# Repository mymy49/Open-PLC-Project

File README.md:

# Open-PLC-Project
yss OS를 사용한 오픈 소스/회로 PLC 프로젝트입니다.

중국의 [LCSC ELECTRONICS](https://www.lcsc.com/)에서 '전자 부품' + 'PCB' + 'SMT' 주문을 한번에 진행할 수 있는 자료를 모두 오픈할 계획입니다. 
누구나 PCB를 주문해서 거의 완성된 상태로 받아볼 수 있도록 할 계획입니다.
보드의 전체 기능이 yss OS 기반에서 제어 가능한 소스코드를 다운로드하여 필요한 동작을 구현하는 프로젝트입니다.

# 사용 프로그램
* 회로도/PCB : Kicad (<https://www.kicad.org/>)
* Compiler + IDE : gcc + Crossworks for ARM (<https://www.rowley.co.uk/arm/index.htm>)
* Office : Libreoffice (<https://www.libreoffice.org/>)

# Base Board
Base Board는 기본적인 소량의 디지털 I/O, 릴레이, AIN, AOUT을 갖출 계획입니다. 
부족한 기능은 외부에 보드를 추가해 CAN으로 서로 통신하며 기능을 보완하는 것을 계획하고 있습니다.

케이스 : <https://ko.aliexpress.com/item/1005003779239575.html?spm=a2g0o.order_list.order_list_main.5.185e140fnb0dcr&gatewayAdapt=glo2kor>

## 단자 구성
케이스는 총 40핀으로 구성되어 있습니다. 
핀맵은 아래와 같이 구성됩니다.

1. [전원] +8~24V (프리볼트)
2. [전원] GND
3. [통신] CANL
4. [통신] CANH

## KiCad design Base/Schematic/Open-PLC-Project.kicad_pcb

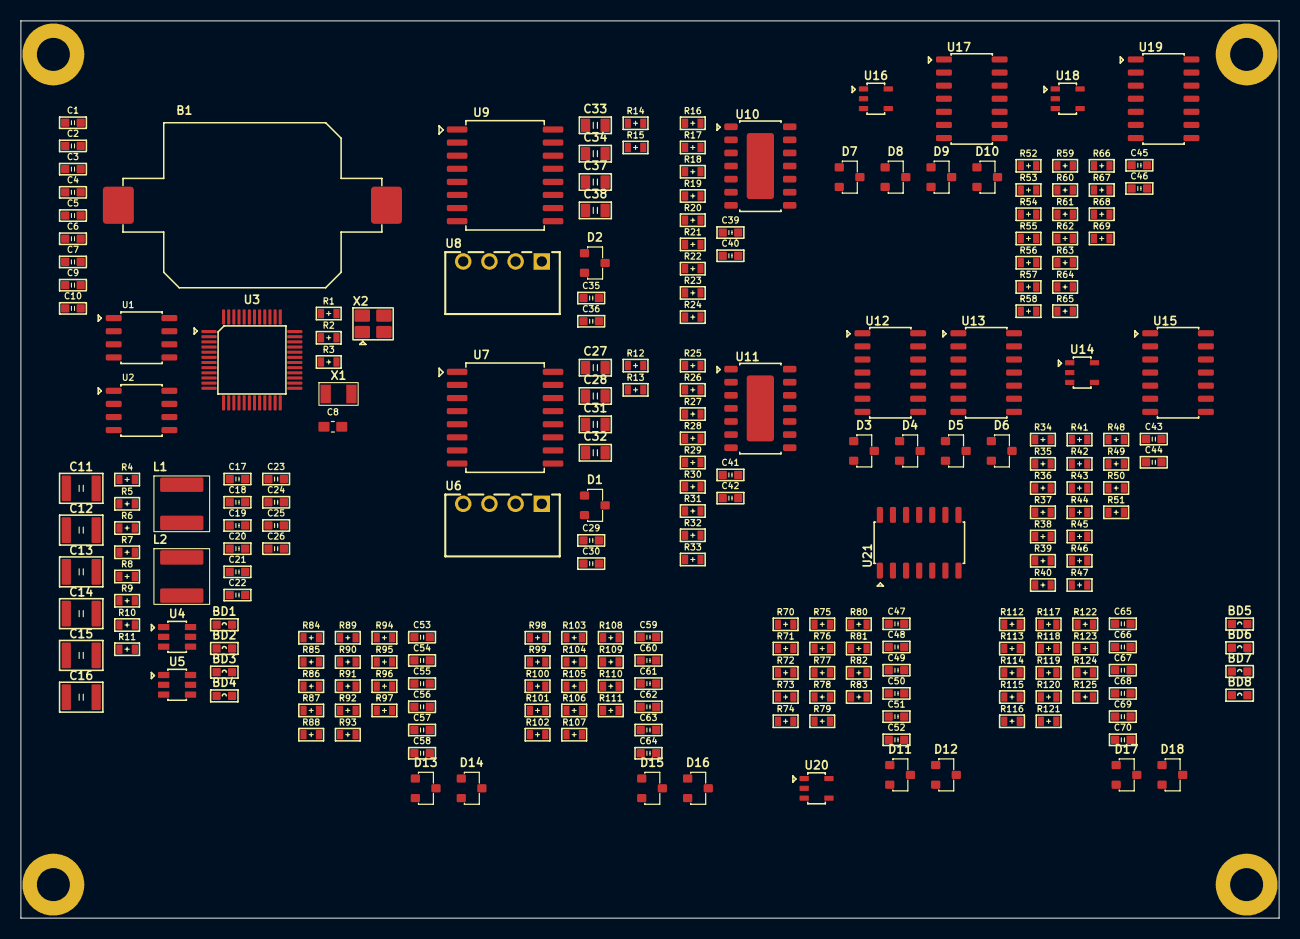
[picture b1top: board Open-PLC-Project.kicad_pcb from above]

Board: 2 copper layers, 122.0 x 87.0 mm, 251 parts (0 on the bottom side), 140 nets, no tracks yet.

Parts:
B1: GT-CR1632-1Au
BD1, BD2, BD3, BD4, BD5, BD6, BD7, BD8: BLM18KG121TN1D; 0603
C1, C4, C7, C9, C10, C17, C18, C19, C20, C21, C22, C29, C30, C35, C36, C40, C42, C43, C44, C45, C46, C47, C51, C52, C53, C57, C58, C59, C63, C64, C65, C69, C70: 0603B104K500; 0603
C2, C3, C5, C6: 0603N120J500; 0603
C8: 0603X225K100; C_0603_1608Metric_Pad1.08x0.95mm_HandSolder
C11, C12, C13, C14, C15, C16: 1210B225K101; 1210
C23, C24, C25, C26: 0603X106K100; 0603
C27, C28, C33, C34: 1206B225K500; 0805
C31, C32, C37, C38: 0805B475K160; 0805
C39, C41, C48, C49, C50, C54, C55, C56, C60, C61, C62, C66, C67, C68: 0603B101K500; 0603
D1: NUP2105LT1G; SOT23
D2: PSM712-ES; SOT23
D3, D4, D5, D6, D7, D8, D9, D10, D11, D12, D13, D14, D15, D16, D17, D18: KDS226; SOT23
H1, H2, H3, H4: HOLE-PAD-7.0-3.2; Hole_7_0_3_2
L1, L2: SWPA5040S150MT; SWPA5040S
R1, R2, R23, R32, R34, R36, R37, R38, R39, R40, R41, R42, R43, R44, R45, R46, R47, R52, R54, R55, R56, R57, R58, R59, R60, R61, R62, R63, R64, R65: WR06X4701FTL; 0603
R3: WR06W3R30FTL; 0603
R4, R6: WR06X4123FTL; 0603
R5, R7: WR06X2003FTL; 0603
R8: WR06X8872FTL; 0603
R9, R11: WR06X2212FTL; 0603
R10: WR06X5102FTL; 0603
R12, R13, R14, R15: WR06X0000JTL; 0603
R16, R17, R18, R19, R20, R21, R22, R25, R26, R27, R28, R29, R30, R31, R48, R49, R50, R51, R66, R67, R68, R69, R70, R71, R72, R73, R78, R79, R80, R81, R84, R85, R86, R87, R92, R93, R94, R95, R98, R99, R100, R101, R106, R107, R108, R109, R112, R113, R114, R115, R120, R121, R122, R123: WR06X1002FTL; 0603
R24, R33: WR06X1201FTL; 0603
R35, R53: WR06X4700FTL; 0603
R74, R75, R76, R77, R88, R89, R90, R91, R102, R103, R104, R105, R116, R117, R118, R119: WR06X3302FTL; 0603
R82, R83, R96, R97, R110, R111, R124, R125: WR06X1001FTL; 0603
U1: MB85RC16PNF-G-JNE; SOIC-8
U2: SL1307ZN+T; SOIC-8
U3: M433LE8AE; LQFP48
U4, U5: TPS560430XDBV; DBV0006A
U6, U8: B0505S-1W; BXXS-1W
U7: CA-IS3052CW; SOIC-16-WB
U9: CA-IS3082WX; SOIC-16-WB
U10, U11: BTS5200-4EKA; PG-DSO-14-48-EP
U12, U13: LM239DR2G; SOIC-14
U14, U16, U18, U20: LMV321-TR; SOT-23-5L
U15, U17, U19, U21: TP2584-SR; SOIC-14
X1: XKXGI-SUA-32.768K; SMD_3215_2Pin
X2: 1532H4-12000JWPDTSNL; CRSTAL_SMD_3225-4Pin

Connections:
+3.3V: BD5.2, BD7.2, C1.2, C9.2, C10.2, D11.2 (C1), D12.2 (C1), D13.2 (C1), D14.2 (C1), D15.2 (C1), D16.2 (C1), D17.2 (C1), D18.2 (C1), R1.2, R2.2, R3.2, R44.2, R45.2, R46.2, R47.2, R62.2, R63.2, R64.2, R65.2, U1.8 (VCC), U2.8 (VCC), U3.23 (VDD), U3.39 (VDD), U7.1 (VCC1), U9.1 (VCC1)
+5V: C21.2, C23.2, C25.2, C27.2, C28.2, C29.2, C33.2, C34.2, C35.2, L1.2, R8.1, U6.2 (Vin), U8.2 (Vin)
+5V_485: C36.2, C37.2, C38.2, U8.4 (Vout), U9.16 (VCC2)
+5V_CAN: C30.2, C31.2, C32.2, U6.4 (Vout), U7.16 (VCC2)
/AIN1/AIN_OUT+: C49.1, C51.2, D11.3 (A1C2), R79.2, R82.2
/AIN1/AIN_OUT-: C50.1, C52.2, D12.3 (A1C2), R81.2, R83.2
/AIN1/REF: R78.2, R80.2, U14.3 (-), U14.4 (OUT)
/AIN2/AIN_OUT+: C55.1, C57.2, D13.3 (A1C2), R93.2, R96.2
/AIN2/AIN_OUT-: C56.1, C58.2, D14.3 (A1C2), R95.2, R97.2
/AIN2/REF: R92.2, R94.2, U16.3 (-), U16.4 (OUT)
/AIN3/AIN_OUT+: C61.1, C63.2, D15.3 (A1C2), R107.2, R110.2
/AIN3/AIN_OUT-: C62.1, C64.2, D16.3 (A1C2), R109.2, R111.2
/AIN3/REF: R106.2, R108.2, U18.3 (-), U18.4 (OUT)
/AIN4/AIN_OUT+: C67.1, C69.2, D17.3 (A1C2), R121.2, R124.2
/AIN4/AIN_OUT-: C68.1, C70.2, D18.3 (A1C2), R123.2, R125.2
/AIN4/REF: R120.2, R122.2, U20.3 (-), U20.4 (OUT)
/CAN/CANH: D1.1 (A2), R12.2
/CAN/CANL: D1.2 (C1), R13.2
/DIN1/VREF: C43.2, R34.2, R35.2, U12.6 (-), U13.4 (-), U13.8 (-), U13.10 (-)
/DIN2/VREF: C45.2, R52.2, R53.2, U12.4 (-), U12.8 (-), U12.10 (-), U13.6 (-)
/DOUT1/IS: C39.2, R23.1
/DOUT2/IS: C41.2, R32.1
/MCU/OSC_IN: C5.2, U3.13 (PF3/XT1_IN), X2.1
/MCU/OSC_OUT: C6.2, U3.14 (PF2/XT1_OUT), X2.3
/MCU/SCL: R2.1, U1.6 (SCL), U2.6 (SCL)
/MCU/SDA: R1.1, U1.5 (SDA), U2.5 (SDA)
/MCU/X1: C3.2, U2.1 (X1), X1.2
/MCU/X2: C2.2, U2.2 (X2), X1.1
/RS485/A: D2.1 (A2), R14.2
/RS485/B: D2.2 (C1), R15.2
AGND: BD4.2, BD6.1, C47.1, C51.1, C52.1, C53.1, C57.1, C58.1, C59.1, C63.1, C64.1, C65.1, C69.1, C70.1, D11.1 (A2), D12.1 (A2), D13.1 (A2), D14.1 (A2), D15.1 (A2), D16.1 (A2), D17.1 (A2), D18.1 (A2), R71.2, R85.2, R99.2, R113.2, U3.46 (AVSS), U14.2 (VSS), U15.11 (GND), U16.2 (VSS), U17.11 (GND), U18.2 (VSS), U19.11 (GND), U20.2 (VSS), U21.11 (GND)
A_+3.3V: BD5.1, R70.1, R84.1, R98.1, R112.1, U14.5 (VDD), U16.5 (VDD), U18.5 (VDD), U20.5 (VDD)
A_V_SUPPLY: BD3.2, U15.4 (VCC), U17.4 (VCC), U19.4 (VCC), U21.4 (VCC)
GND: B1.2 (-), BD6.2, BD8.2, C1.1, C2.1, C3.1, C4.1, C5.1, C6.1, C7.1, C8.1, C9.1, C10.1, C39.1, C41.1, U1.4 (VSS), U2.4 (VSS), U3.37 (VSS), U7.2 (GND1), U7.8 (GND1), U9.2 (GND1), U9.7 (GND1), U9.8 (GND1)
GND_485: C36.1, C37.1, C38.1, U8.3 (0V), U9.9 (GND2), U9.10 (GND2), U9.15 (GND2)
GND_CAN: C30.1, C31.1, C32.1, D1.3 (A1C2), D2.3 (A1C2), U6.3 (0V), U7.9 (GND2), U7.10 (GND2), U7.15 (GND2)
unnamed: B1.1 (+), C4.2, U2.3 (VBAT)
unnamed: BD7.1, C22.2, C24.2, C26.2, L2.2, R10.2
unnamed: D3.3 (A1C2), R36.2, R40.1
unnamed: D4.3 (A1C2), R37.2, R41.1
unnamed: D5.3 (A1C2), R38.2, R42.1
unnamed: D6.3 (A1C2), R39.2, R43.1
unnamed: D7.3 (A1C2), R54.2, R58.1
unnamed: D8.3 (A1C2), R55.2, R59.1
unnamed: D9.3 (A1C2), R56.2, R60.1
unnamed: D10.3 (A1C2), R57.2, R61.1
unnamed: C7.2, R3.1, U3.45 (AVDD)
unnamed: C8.2, U3.38 (LDO_CAP)
unnamed: C19.2, U4.1 (CB)
unnamed: R4.1, R5.2, U4.4 (EN)
unnamed: R8.2, R9.2, U4.3 (FB)
unnamed: C19.1, L1.1, U4.6 (SW)
unnamed: BD1.2, C11.2, C13.2, C15.2, C17.2, R4.2, U4.5 (VIN)
unnamed: C20.2, U5.1 (CB)
unnamed: R6.1, R7.2, U5.4 (EN)
unnamed: R10.1, R11.2, U5.3 (FB)
unnamed: C20.1, L2.1, U5.6 (SW)
unnamed: BD2.2, C12.2, C14.2, C16.2, C18.2, R6.2, U5.5 (VIN)
unnamed: R12.1, U7.13 (CANH)
unnamed: R13.1, U7.12 (CANL)
unnamed: R14.1, U9.12 (A)
unnamed: R15.1, U9.13 (B)
unnamed: R20.2, U10.10 (DEN)
unnamed: R21.2, U10.5 (DSEL0)
unnamed: R22.2, U10.4 (DSEL1)
unnamed: R16.2, U10.7 (IN0)
unnamed: R17.2, U10.6 (IN1)
unnamed: R18.2, U10.8 (IN2)
unnamed: R19.2, U10.9 (IN3)
unnamed: R23.2, R24.2, U10.12 (IS)
unnamed: R29.2, U11.10 (DEN)
unnamed: R30.2, U11.5 (DSEL0)
unnamed: R31.2, U11.4 (DSEL1)
unnamed: R25.2, U11.7 (IN0)
unnamed: R26.2, U11.6 (IN1)
unnamed: R27.2, U11.8 (IN2)
unnamed: R28.2, U11.9 (IN3)
unnamed: R32.2, R33.2, U11.12 (IS)
unnamed: R40.2, U12.7 (+)
unnamed: R44.1, R48.1, U12.1 (OUT)
unnamed: R59.2, U12.5 (+)
unnamed: R63.1, R67.1, U12.2 (OUT)
unnamed: R60.2, U12.9 (+)
unnamed: R64.1, R68.1, U12.14 (OUT)
unnamed: R61.2, U12.11 (+)
unnamed: R65.1, R69.1, U12.13 (OUT)
unnamed: R58.2, U13.7 (+)
unnamed: R62.1, R66.1, U13.1 (OUT)
unnamed: R41.2, U13.5 (+)
unnamed: R45.1, R49.1, U13.2 (OUT)
unnamed: R42.2, U13.9 (+)
unnamed: R46.1, R50.1, U13.14 (OUT)
unnamed: R43.2, U13.11 (+)
unnamed: R47.1, R51.1, U13.13 (OUT)
unnamed: C47.2, R70.2, R71.1, U14.1 (+)
unnamed: C48.1, R72.2, U15.3 (+)
unnamed: R74.1, R77.1, U15.1 (OUT), U15.2 (-)
unnamed: C48.2, R73.2, U15.5 (+)
unnamed: R75.1, R76.1, U15.6 (-), U15.7 (OUT)
unnamed: R74.2, R78.1, U15.10 (+)
unnamed: C49.2, R75.2, R79.1, U15.9 (-)
unnamed: R82.1, U15.8 (OUT)
unnamed: R76.2, R80.1, U15.12 (+)
unnamed: C50.2, R77.2, R81.1, U15.13 (-)
unnamed: R83.1, U15.14 (OUT)
unnamed: C53.2, R84.2, R85.1, U16.1 (+)
unnamed: C54.1, R86.2, U17.3 (+)
unnamed: R88.1, R91.1, U17.1 (OUT), U17.2 (-)
unnamed: C54.2, R87.2, U17.5 (+)
unnamed: R89.1, R90.1, U17.6 (-), U17.7 (OUT)
unnamed: R88.2, R92.1, U17.10 (+)
unnamed: C55.2, R89.2, R93.1, U17.9 (-)
unnamed: R96.1, U17.8 (OUT)
unnamed: R90.2, R94.1, U17.12 (+)
unnamed: C56.2, R91.2, R95.1, U17.13 (-)
unnamed: R97.1, U17.14 (OUT)
unnamed: C59.2, R98.2, R99.1, U18.1 (+)
unnamed: C60.1, R100.2, U19.3 (+)
unnamed: R102.1, R105.1, U19.1 (OUT), U19.2 (-)
unnamed: C60.2, R101.2, U19.5 (+)
unnamed: R103.1, R104.1, U19.6 (-), U19.7 (OUT)
unnamed: R102.2, R106.1, U19.10 (+)
unnamed: C61.2, R103.2, R107.1, U19.9 (-)
unnamed: R110.1, U19.8 (OUT)
unnamed: R104.2, R108.1, U19.12 (+)
unnamed: C62.2, R105.2, R109.1, U19.13 (-)
unnamed: R111.1, U19.14 (OUT)
unnamed: C65.2, R112.2, R113.1, U20.1 (+)
unnamed: C66.1, R114.2, U21.3 (+)
unnamed: R116.1, R119.1, U21.1 (OUT), U21.2 (-)
unnamed: C66.2, R115.2, U21.5 (+)
unnamed: R117.1, R118.1, U21.6 (-), U21.7 (OUT)
unnamed: R116.2, R120.1, U21.10 (+)
unnamed: C67.2, R117.2, R121.1, U21.9 (-)
unnamed: R124.1, U21.8 (OUT)
unnamed: R118.2, R122.1, U21.12 (+)
unnamed: C68.2, R119.2, R123.1, U21.13 (-)
unnamed: R125.1, U21.14 (OUT)
PGND: BD4.1, BD8.1, C11.1, C12.1, C13.1, C14.1, C15.1, C16.1, C17.1, C18.1, C21.1, C22.1, C23.1, C24.1, C25.1, C26.1, C27.1, C28.1, C29.1, C33.1, C34.1, C35.1, C40.1, C42.1, C43.1, C44.1, C45.1, C46.1, D3.1 (A2), D4.1 (A2), D5.1 (A2), D6.1 (A2), D7.1 (A2), D8.1 (A2), D9.1 (A2), D10.1 (A2), R5.1, R7.1, R9.1, R11.1, R24.1, R33.1, R35.1, R53.1, U4.2 (GND), U5.2 (GND), U6.1 (GND), U8.1 (GND), U10.11 (GND), U11.11 (GND), U12.12 (GND), U13.12 (GND)
V_SUPPLY: BD1.1, BD2.1, BD3.1, C40.2, C42.2, C44.2, C46.2, D3.2 (C1), D4.2 (C1), D5.2 (C1), D6.2 (C1), D7.2 (C1), D8.2 (C1), D9.2 (C1), D10.2 (C1), R34.1, R52.1, U10.EP (VS), U11.EP (VS), U12.3 (VCC), U13.3 (VCC)

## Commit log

2024-12-01 [회로도 등록] - 테스트를 위해 MCU 하나만 올린 회로도면을 추가함
2024-12-01 [폴더 구조 변경] - 회로도 일부 업데이트
2024-12-01 [소스 코드 추가]
2024-12-01 [Base 회로 업데이트] - 전원 회로 추가
2024-12-01 [BOM 문서 테스트] - Libreoffice로 BOM 문서 출력 테스트 - 회로도에 CAN transceiver 추가
2024-12-03 [Base 회로도 업데이트] - MCU를 STM32F446 -> Nuvoton M433으로 변경
2024-12-07 [Base 횔로도 업데이트] - CAN 통신용 5V 절연된 전원 추가
2024-12-07 [Base 회로도 업데이트] - 5V 전원 추가 - 3.3V, 5V 회로도 보완
2024-12-07 [Base 회로도 업데이트] - RTC 회로 추가 - M433에는 VBAT 단자가 없어서 별도 부품으로 추가함
2024-12-07 Update README.md
    - 소개 내용 추가
    - 사용 프로그램 추가
    - Base 보드에 관한 소개
    - 단자 구성 일부 추가
2024-12-07 Update README.md
    - LCSC 표기 변경 및 링크 추가
2024-12-14 [Base 회로도 업데이트] - RS485 회로 추가
2024-12-14 [Base 회로도 업데이트] - RS485, CAN 보호회로 추가
2024-12-14 [Base 회로도 업데이트] - DOUT 회로 추가
2024-12-14 [Base 회로도 업데이트] - DOUT 출력을 4개에서 8개로 늘림
2024-12-14 [Base PCB 업데이트] - PCB 외곽선과 볼트 위치 설정
2024-12-14 [Base 회로도 업데이트] - DIN 입력 8개 추가
2024-12-15 [Base 회로도 업데이트] - AIN 입력 4개 추가
